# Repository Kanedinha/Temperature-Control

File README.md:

# Temperature-Control
 Assingment for Mecatronic subject of IPB

The main idea is use a triac and a optocoupler to control the number of sinusoidal cycles over the Load, so we can control de RMS Voltage over the Load. that circuit can be called as a solid state relay, this circuit already have modules projected to work in high voltage and high current.

To complete de feedback loop, we can use a simple NTC sensor. So the following schema is projected that way

The following block diagram is used to model the system:

One detail that impact the dinamic of system is de distance of the sensor from the heater, this mean the system have a slow response of the air temperature. this detail need to include in the system modeling.

For the PCB we can use the KiCAD project to guide us how to make an PCB, because how we will use a high voltage electrical network (230 Vrms; 50 Hz - in Portugal), its better use a PCB than a breadboard.

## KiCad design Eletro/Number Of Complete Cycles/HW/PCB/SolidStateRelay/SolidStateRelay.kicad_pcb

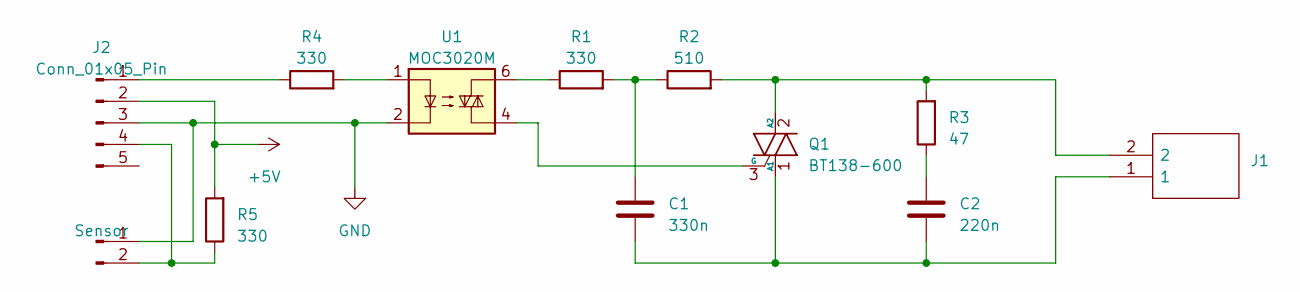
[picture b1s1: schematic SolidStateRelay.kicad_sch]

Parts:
C1: 330n; C_Rect_L9.0mm_W3.3mm_P7.50mm_MKT
C2: 220n; C_Rect_L9.0mm_W3.3mm_P7.50mm_MKT
J1: KRE_02; KRE02; Manufacturer_Part_Number KRE 02
J2: Conn_01x05_Pin; JST_EH_S5B-EH_1x05_P2.50mm_Horizontal
Q1: BT138-600; TO-220-3_Vertical
R1, R4, R5: 330; R_Axial_DIN0207_L6.3mm_D2.5mm_P10.16mm_Horizontal
R2: 510; R_Axial_DIN0207_L6.3mm_D2.5mm_P10.16mm_Horizontal
R3: 47; R_Axial_DIN0207_L6.3mm_D2.5mm_P10.16mm_Horizontal
Sensor: PinHeader_1x02_P2.54mm_Vertical
U1: MOC3020M; DIP-6_W7.62mm_LongPads

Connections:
+5V: J2.2, R5.2
GND: J2.3, Sensor.1, U1.2
unnamed: C1.1, R1.2, R2.1
unnamed: C2.1, R3.1
unnamed: J2.1, R4.1
unnamed: J2.4, R5.1, Sensor.2
unnamed: C1.2, C2.2, J1.1, Q1.1 (A1)
unnamed: J1.2, Q1.2 (A2), R2.2, R3.2
unnamed: Q1.3 (G), U1.4
unnamed: R1.1, U1.6
unnamed: R4.2, U1.1

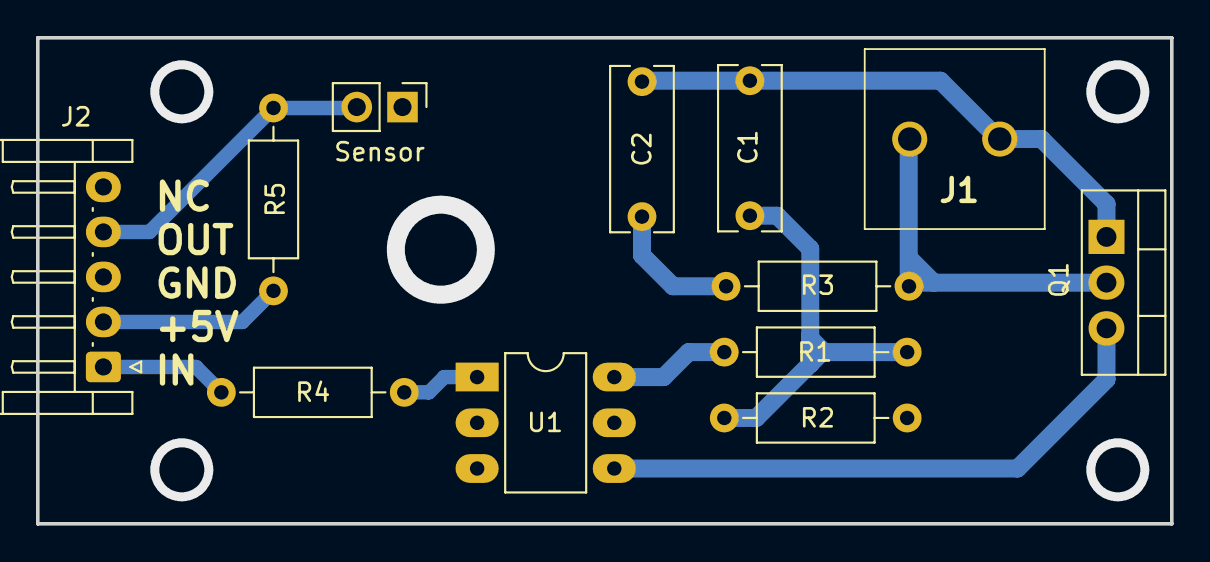
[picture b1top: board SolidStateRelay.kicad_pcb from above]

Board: 2 copper layers, 63.0 x 27.0 mm, 12 parts (0 on the bottom side), 11 nets.

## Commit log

2023-12-20 project is working
2023-12-27 PCB update
2023-12-27 images
2023-12-27 schema image
2023-12-27 kicad some zip file
2023-12-30 New images of structure
2023-12-30 Block Diagram update
2023-12-30 update block diagram
2024-01-02 final schematic
2024-01-03 System Modeling and update some images
2024-07-24 i dont know
